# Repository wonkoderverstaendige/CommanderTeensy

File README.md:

# CommanderTeensy
Experimental setup monitor and controller
```
$ cd web
$ python ../commander_teensy/receiver.py
```
Runs webserver on localhost:8000

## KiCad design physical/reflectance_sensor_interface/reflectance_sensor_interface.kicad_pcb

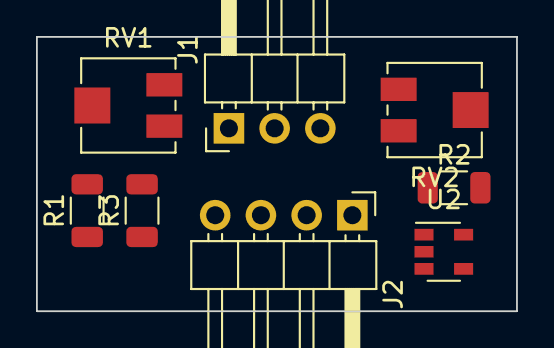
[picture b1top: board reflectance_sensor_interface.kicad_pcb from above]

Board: 2 copper layers, 26.7 x 15.2 mm, 8 parts (0 on the bottom side), 8 nets, no tracks yet.

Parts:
J1: Conn_01x03_Male; PinHeader_1x03_P2.54mm_Horizontal
J2: Conn_01x04_Female; PinHeader_1x04_P2.54mm_Horizontal
R1: 47; R_1206_3216Metric
R2, R3: 100; R_1206_3216Metric
RV1: 1k; Potentiometer_Vishay_TS53YJ_Vertical
RV2: 20k; Potentiometer_Vishay_TS53YJ_Vertical
U2: LM321; SOT-23-5

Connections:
+3V3: J1.3, RV1.1, RV2.1, U2.5
Ln: J1.1, J2.2, J2.4, U2.2
Lp: J2.1, R1.2
unnamed: J1.2, R3.1
unnamed: R1.1, RV1.2
unnamed: R2.1, RV2.2
unnamed: R3.2, U2.3, U2.4
Tc: J2.3, R2.2, U2.1

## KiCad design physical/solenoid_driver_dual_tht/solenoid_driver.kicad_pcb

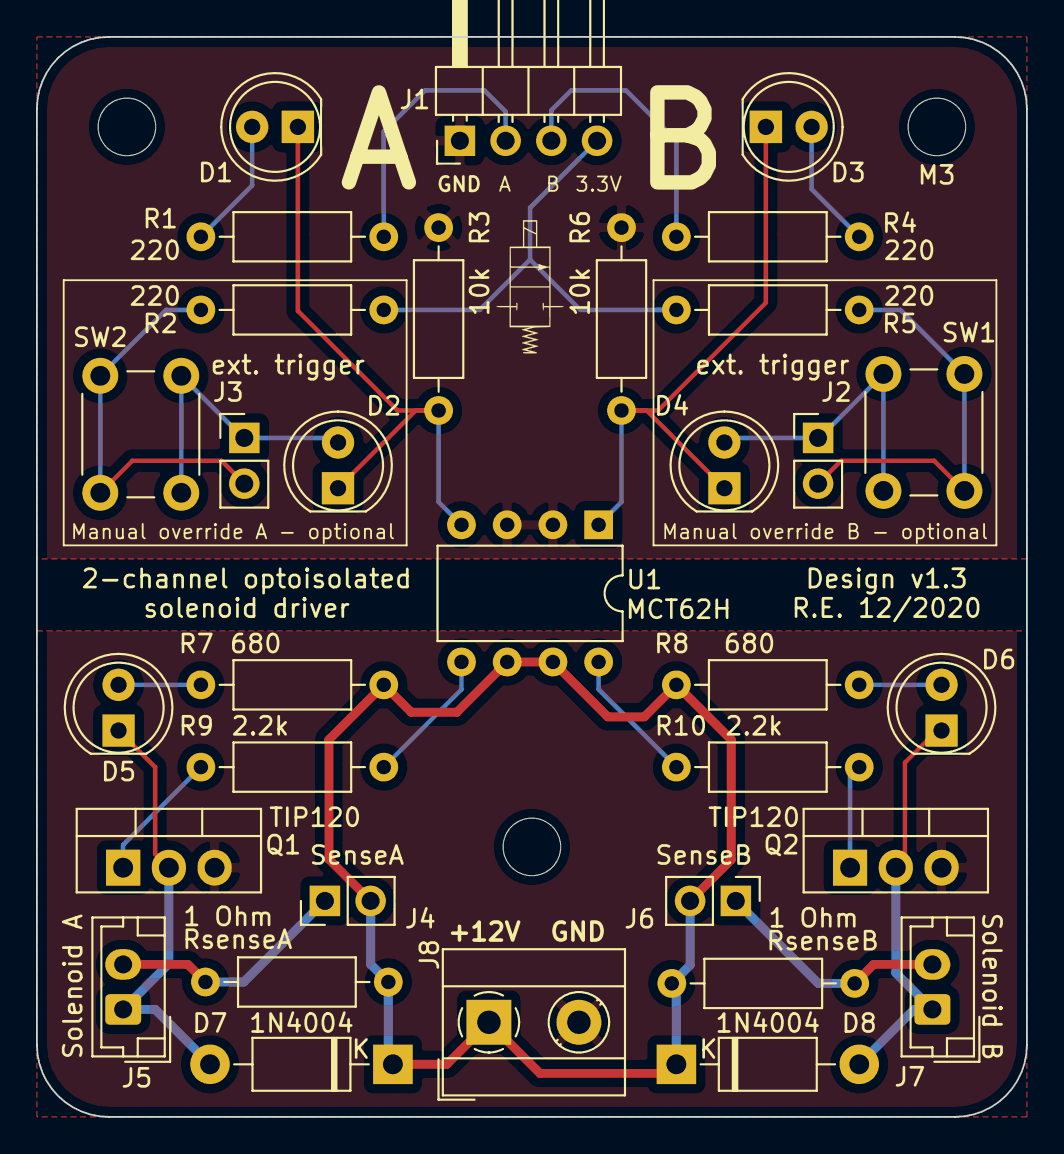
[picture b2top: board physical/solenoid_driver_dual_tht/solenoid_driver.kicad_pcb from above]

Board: 2 copper layers, 55.0 x 60.0 mm, 36 parts (0 on the bottom side), 24 nets.

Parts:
D1, D2, D3, D4, D5, D6: LED; LED_D5.0mm
D7, D8: 1N4004; D_DO-41_SOD81_P10.16mm_Horizontal
J1: Input Header; PinHeader_1x04_P2.54mm_Horizontal
J2: Solenoid B Override; PinHeader_1x02_P2.54mm_Vertical
J3: Solenoid A Override; PinHeader_1x02_P2.54mm_Vertical
J4: SenseA; PinHeader_1x02_P2.54mm_Vertical
J5: Solenoid A; JST_EH_B2B-EH-A_1x02_P2.50mm_Vertical
J6: SenseB; PinHeader_1x02_P2.54mm_Vertical
J7: Solenoid B; JST_EH_B2B-EH-A_1x02_P2.50mm_Vertical
J8: 12V Input; TerminalBlock_MetzConnect_Type055_RT01502HDWU_1x02_P5.00mm_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
M3, M3#2, M3#3: MountingHole_3.2mm_M3
Q1, Q2: TIP120; TO-220-3_Vertical
R1, R2, R4, R5: 220; R_Axial_DIN0207_L6.3mm_D2.5mm_P10.16mm_Horizontal
R3, R6: 10k; R_Axial_DIN0207_L6.3mm_D2.5mm_P10.16mm_Horizontal
R7, R8: 680; R_Axial_DIN0207_L6.3mm_D2.5mm_P10.16mm_Horizontal
R9, R10: 2.2k; R_Axial_DIN0207_L6.3mm_D2.5mm_P10.16mm_Horizontal
RsenseA: 1 Ohm; R_Axial_DIN0207_L6.3mm_D2.5mm_P10.16mm_Horizontal
RsenseB: 1 Ohm; R_Axial_DIN0207_L6.3mm_D2.5mm_P10.16mm_Horizontal
SW1, SW2: SW_Push; SW_PUSH_6mm
U1: MCT62H; DIP-8_W7.62mm

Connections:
3.3V: J1.4, R2.2, R5.2
12V: D7.1, D8.1, J4.2, J6.2, J8.1, R7.2, R8.2, RsenseA.1, RsenseB.1, U1.6, U1.7
GNDPWR: J8.2, Q1.3, Q2.3
InputA: J1.2, R1.2
InputB: J1.3, R4.2
unnamed: D1.1, D2.1, R3.2, U1.4
unnamed: D1.2, R1.1
unnamed: D2.2, J3.1, SW2.2
unnamed: D3.1, D4.1, R6.1, U1.1
unnamed: D3.2, R4.1
unnamed: D4.2, J2.1, SW1.2
unnamed: D5.1, D7.2, J5.1, Q1.2
unnamed: D5.2, R7.1
unnamed: D6.1, D8.2, J7.1, Q2.2
unnamed: D6.2, R8.1
unnamed: J2.2, R5.1, SW1.1
unnamed: J3.2, R2.1, SW2.1
unnamed: J4.1, J5.2, RsenseA.2
unnamed: J6.1, J7.2, RsenseB.2
unnamed: Q1.1, R9.1
unnamed: Q2.1, R10.1
unnamed: R9.2, U1.5
unnamed: R10.2, U1.8
TeensyGND: J1.1, R3.1, R6.2, U1.2, U1.3

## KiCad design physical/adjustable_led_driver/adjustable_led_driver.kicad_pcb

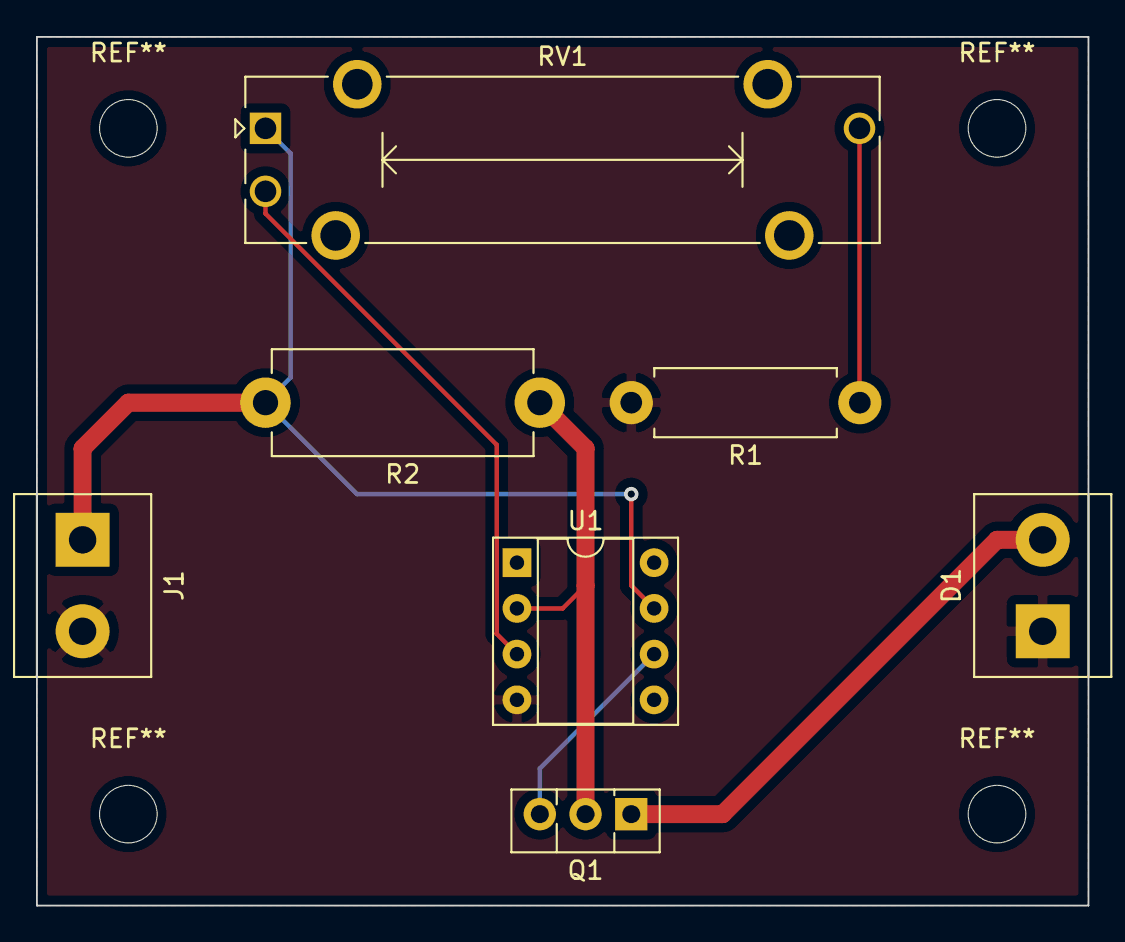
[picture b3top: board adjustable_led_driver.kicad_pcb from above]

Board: 2 copper layers, 58.4 x 48.3 mm, 7 parts (0 on the bottom side), 7 nets.

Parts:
D1: LED; TerminalBlock_bornier-2_P5.08mm
J1: Conn_01x02_Male; TerminalBlock_bornier-2_P5.08mm
Q1: BD140; TO-126-3_Vertical
R1: 1k; R_Axial_DIN0411_L9.9mm_D3.6mm_P12.70mm_Horizontal
R2: 10; R_Axial_DIN0614_L14.3mm_D5.7mm_P15.24mm_Horizontal
RV1: 20k; Potentiometer_Bourns_PTA2043_Single_Slide
U1: LM741; DIP-8_W7.62mm_Socket

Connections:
+5V: J1.1, R2.2, RV1.1, U1.7
GND: D1.1, J1.2, R1.2, U1.4
unnamed: D1.2, Q1.1
unnamed: Q1.2, R2.1, U1.2
unnamed: Q1.3, U1.6
unnamed: R1.1, RV1.3
unnamed: RV1.2, U1.3

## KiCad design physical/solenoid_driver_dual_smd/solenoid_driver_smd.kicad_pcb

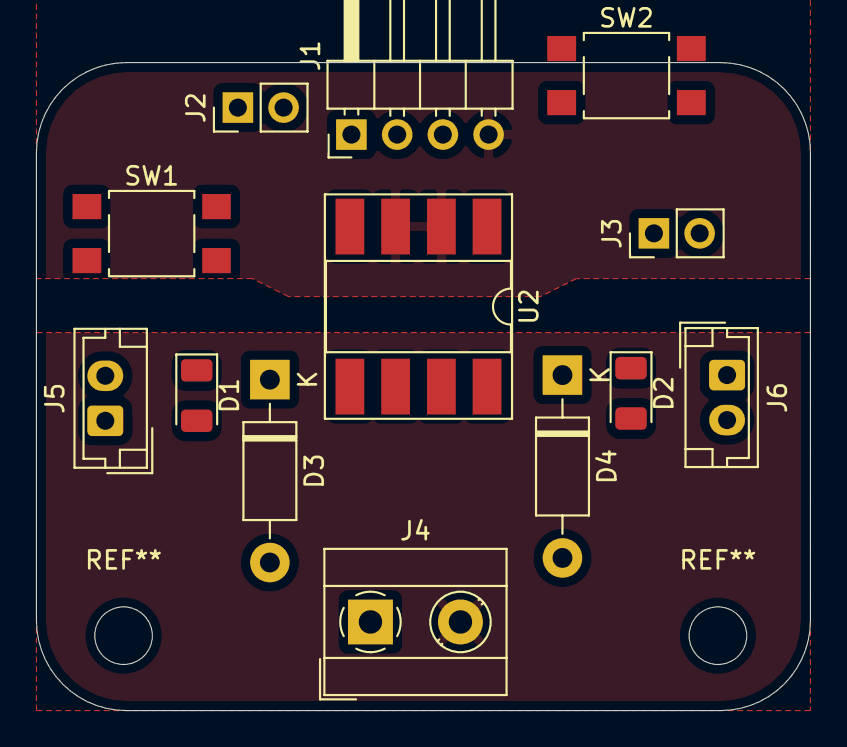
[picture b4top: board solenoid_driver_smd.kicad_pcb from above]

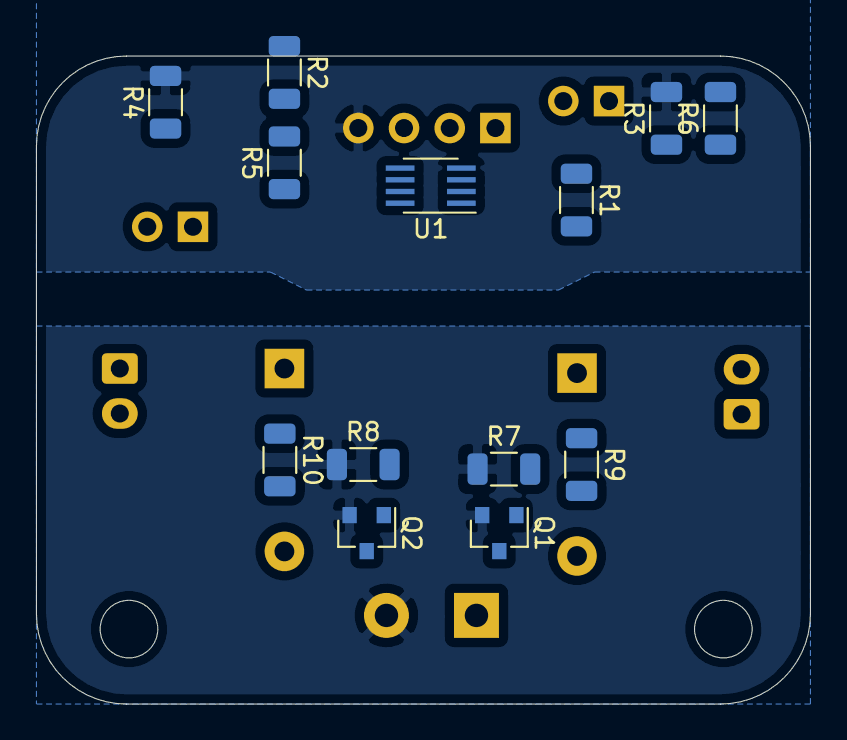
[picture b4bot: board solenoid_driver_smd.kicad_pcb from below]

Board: 2 copper layers, 43.0 x 36.0 mm, 26 parts (13 on the bottom side), 20 nets, no tracks yet.

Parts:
D1, D2: LED; LED_1206_3216Metric
D3, D4: 1N4004; D_DO-41_SOD81_P10.16mm_Horizontal
J1: Input Header; PinHeader_1x04_P2.54mm_Horizontal
J2: ext_trig_A; PinHeader_1x02_P2.54mm_Vertical
J3: ext_trig_B; PinHeader_1x02_P2.54mm_Vertical
J4: PWR12V; TerminalBlock_MetzConnect_Type055_RT01502HDWU_1x02_P5.00mm_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
J5: SolenoidA; JST_EH_B2B-EH-A_1x02_P2.50mm_Vertical
J6: SolenoidB; JST_EH_B2B-EH-A_1x02_P2.50mm_Vertical
Q1, Q2: 2N7002K; SOT-23
R1, R2: 1k; R_1206_3216Metric
R3, R4, R7, R8: 10k; R_1206_3216Metric
R5, R6: 220; R_1206_3216Metric
R9, R10: 680; R_1206_3216Metric
SW1: man_trig_A; SW_SPST_TL3305A
SW2: man_trig_B; SW_SPST_TL3305A
U1: 74LVC2G32; SSOP-8_2.95x2.8mm_P0.65mm
U2: MCT62H; DIP-8_W8.89mm_SMDSocket_LongPads

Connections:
3.3V: J1.1, R1.2, R2.2, U1.8
12V: D3.1, D4.1, J4.1, J5.2, J6.2, R9.1, R10.1, U2.6, U2.7
GNDPWR: J4.2, Q1.2, Q2.2, R7.1, R8.1
InputA: J1.2, U1.1
InputB: J1.3, U1.5
unnamed: D1.1, D3.2, J5.1, Q1.3
unnamed: D1.2, R9.2
unnamed: D2.1, D4.2, J6.1, Q2.3
unnamed: D2.2, R10.2
unnamed: J2.1, R3.1, SW1.2, U1.2
unnamed: J2.2, R1.1, SW1.1
unnamed: J3.1, R4.1, SW2.2, U1.6
unnamed: J3.2, R2.1, SW2.1
unnamed: Q1.1, R7.2, U2.8
unnamed: Q2.1, R8.2, U2.5
unnamed: R5.1, U2.1
unnamed: R5.2, U1.7
unnamed: R6.1, U2.4
unnamed: R6.2, U1.3
TeensyGND: J1.4, R3.2, R4.2, U1.4, U2.2, U2.3

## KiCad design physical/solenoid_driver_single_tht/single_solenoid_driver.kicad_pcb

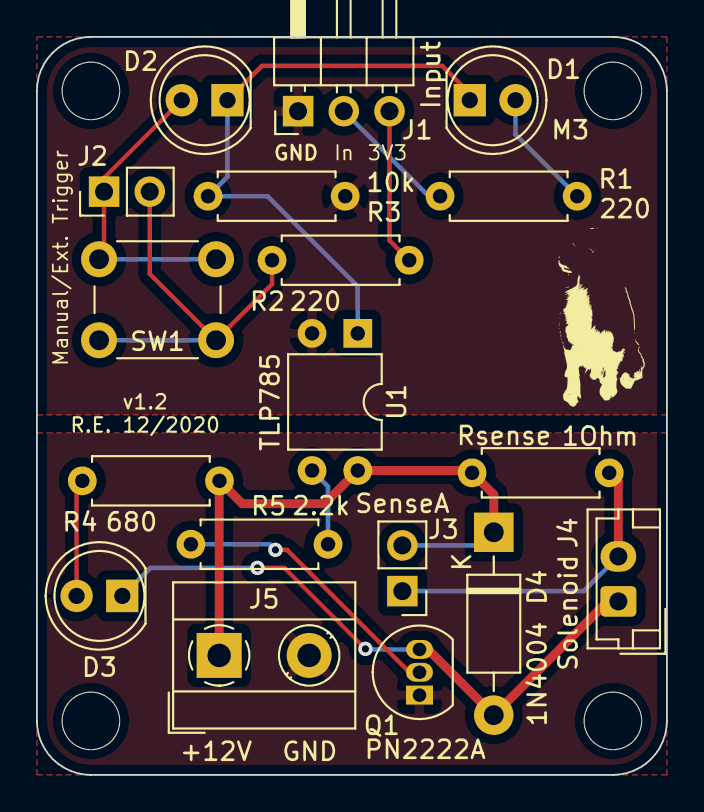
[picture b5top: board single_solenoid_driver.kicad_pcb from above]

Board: 2 copper layers, 35.0 x 41.0 mm, 22 parts (0 on the bottom side), 14 nets.

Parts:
D1, D2, D3: LED; LED_D5.0mm
D4: 1N4004; D_DO-41_SOD81_P10.16mm_Horizontal
J1: Input; PinHeader_1x03_P2.54mm_Horizontal
J2: Manual/External Trigger; PinHeader_1x02_P2.54mm_Vertical
J3: SenseA; PinHeader_1x02_P2.54mm_Vertical
J4: Solenoid; JST_EH_B2B-EH-A_1x02_P2.50mm_Vertical
J5: 12V Input; TerminalBlock_MetzConnect_Type055_RT01502HDWU_1x02_P5.00mm_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
M3, M3#2, M3#3, M3#4: MountingHole_3.2mm_M3
Q1: PN2222A; TO-92_Inline
R1, R2: 220; R_Axial_DIN0207_L6.3mm_D2.5mm_P7.62mm_Horizontal
R3: 10k; R_Axial_DIN0207_L6.3mm_D2.5mm_P7.62mm_Horizontal
R4: 680; R_Axial_DIN0207_L6.3mm_D2.5mm_P7.62mm_Horizontal
R5: 2.2k; R_Axial_DIN0207_L6.3mm_D2.5mm_P7.62mm_Horizontal
Rsense: 1Ohm; R_Axial_DIN0207_L6.3mm_D2.5mm_P7.62mm_Horizontal
SW1: SW_Push; SW_PUSH_6mm
U1: TLP785; DIP-4_W7.62mm

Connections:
3.3V: J1.3, R2.2
12V: D4.1, J3.2, J5.1, R4.2, Rsense.1, U1.4
GNDPWR: J5.2, Q1.1
InputA: J1.2, R1.2
unnamed: D1.1, D2.1, R3.2, U1.1
unnamed: D1.2, R1.1
unnamed: D2.2, J2.1, SW1.2
unnamed: D3.1, D4.2, J4.1, Q1.3
unnamed: D3.2, R4.1
unnamed: J2.2, R2.1, SW1.1
unnamed: J3.1, J4.2, Rsense.2
unnamed: Q1.2, R5.1
unnamed: R5.2, U1.3
TeensyGND: J1.1, R3.1, U1.2

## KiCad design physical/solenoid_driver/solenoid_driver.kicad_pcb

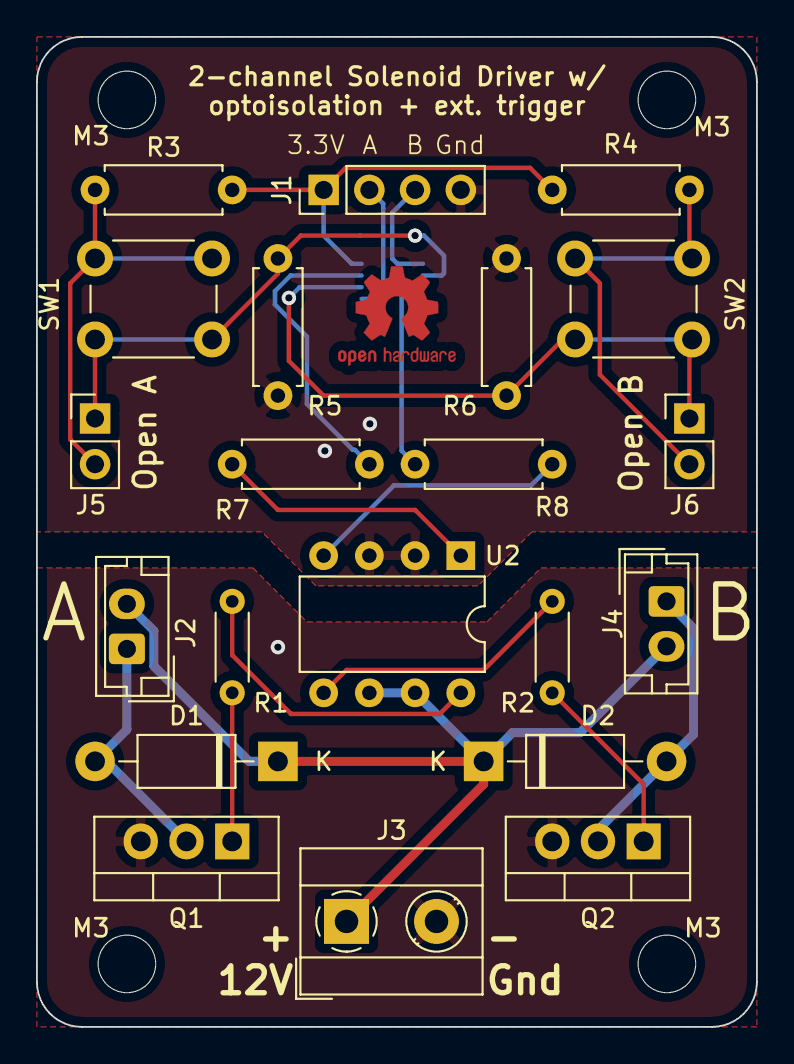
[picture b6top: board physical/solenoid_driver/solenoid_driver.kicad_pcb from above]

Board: 2 copper layers, 40.0 x 55.0 mm, 26 parts (1 on the bottom side), 20 nets.

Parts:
D1, D2: 1N4004; D_DO-41_SOD81_P10.16mm_Horizontal
J1: Input Header; PinHeader_1x04_P2.54mm_Vertical
J2: Solenoid A; JST_EH_B2B-EH-A_1x02_P2.50mm_Vertical
J3: 12V Input; TerminalBlock_MetzConnect_Type055_RT01502HDWU_1x02_P5.00mm_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
J4: Solenoid B; JST_EH_B2B-EH-A_1x02_P2.50mm_Vertical
J5: Solenoid A Override; PinHeader_1x02_P2.54mm_Vertical
J6: Solenoid B Override; PinHeader_1x02_P2.54mm_Vertical
M3, M3#2, M3#3, M3#4: MountingHole_3.2mm_M3
Q1, Q2: TIP120; TO-220-3_Vertical
R1, R2: 2.2k; R_Axial_DIN0204_L3.6mm_D1.6mm_P5.08mm_Horizontal
R3, R4: 1k; R_Axial_DIN0207_L6.3mm_D2.5mm_P7.62mm_Horizontal
R5, R6: 10k; R_Axial_DIN0207_L6.3mm_D2.5mm_P7.62mm_Horizontal
R7, R8: 220; R_Axial_DIN0207_L6.3mm_D2.5mm_P7.62mm_Horizontal
SW1, SW2: SW_Push; SW_PUSH_6mm
U1: 74LVC2G32; SSOP-8_2.95x2.8mm_P0.65mm
U2: ILD74; DIP-8_W7.62mm

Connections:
3.3V: J1.1, R3.2, R4.2, U1.8
12V: D1.1, D2.1, J2.2, J3.1, J4.2, U2.6, U2.7
GNDPWR: J3.2, Q1.3, Q2.3
InputA: J1.3, U1.1
InputB: J1.2, U1.5
unnamed: D1.2, J2.1, Q1.2
unnamed: D2.2, J4.1, Q2.2
unnamed: J5.1, R5.2, SW1.2, U1.2
unnamed: J5.2, R3.1, SW1.1
unnamed: J6.1, R6.2, SW2.2, U1.6
unnamed: J6.2, R4.1, SW2.1
unnamed: Q1.1, R1.1
unnamed: Q2.1, R2.1
unnamed: R1.2, U2.8
unnamed: R2.2, U2.5
unnamed: R7.1, U2.1
unnamed: R7.2, U1.7
unnamed: R8.1, U2.4
unnamed: R8.2, U1.3
TeensyGND: J1.4, R5.1, R6.1, U1.4, U2.2, U2.3

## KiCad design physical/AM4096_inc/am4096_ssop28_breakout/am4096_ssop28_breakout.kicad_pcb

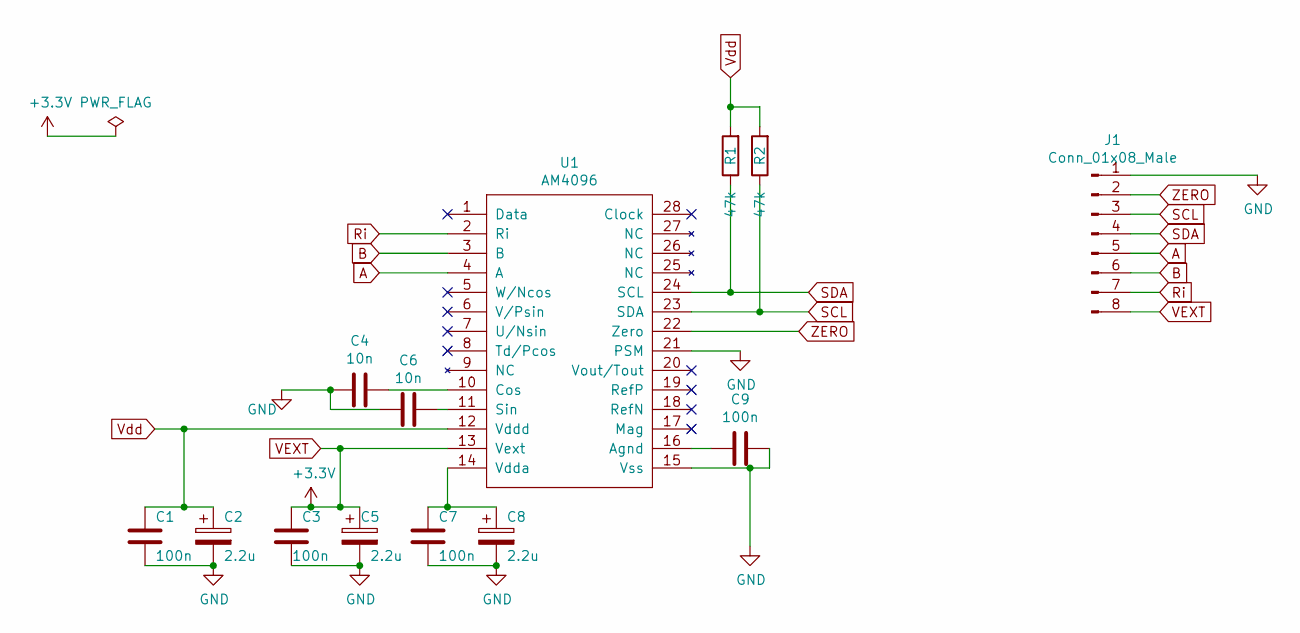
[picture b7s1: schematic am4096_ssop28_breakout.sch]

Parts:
C1, C3, C7: 100n; CP_EIA-3216-18_Kemet-A
C2, C5, C8: 2.2u; CP_EIA-3216-18_Kemet-A
C4, C6: 10n; C_1206_3216Metric
C9: 100n; C_1206_3216Metric
J1: Conn_01x08_Male; Socket_Strip_Straight_1x08_Pitch2.54mm
R1, R2: 47k; R_1206_3216Metric
U1: AM4096; SSOP-28_5.3x10.2mm_P0.65mm

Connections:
A: J1.5, U1.4 (A)
B: J1.6, U1.3 (B)
GND: C1.2, C2.2, C3.2, C4.2, C5.2, C6.2, C7.2, C8.2, C9.1, J1.1, U1.15 (Vss), U1.21 (PSM)
unnamed: C4.1, U1.10 (Cos)
unnamed: C6.1, U1.11 (Sin)
unnamed: C7.1, C8.1, U1.14 (Vdda)
unnamed: C9.2, U1.16 (Agnd)
Ri: J1.7, U1.2 (Ri)
SCL: J1.3, R2.1, U1.23 (SDA)
SDA: J1.4, R1.1, U1.24 (SCL)
VEXT: C3.1, C5.1, J1.8, U1.13 (Vext)
Vdd: C1.1, C2.1, R1.2, R2.2, U1.12 (Vddd)
ZERO: J1.2, U1.22 (Zero)

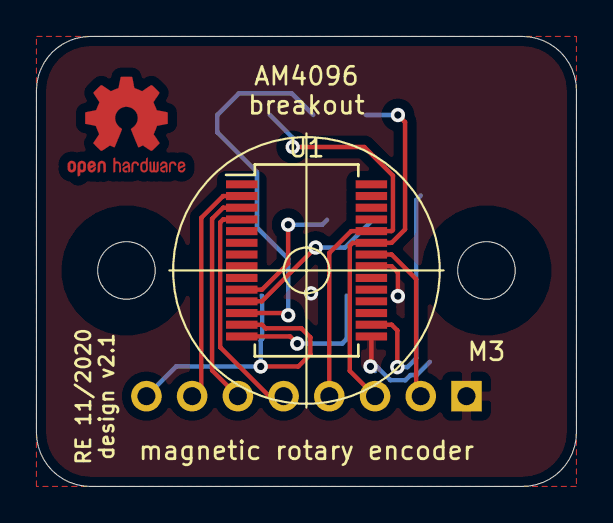
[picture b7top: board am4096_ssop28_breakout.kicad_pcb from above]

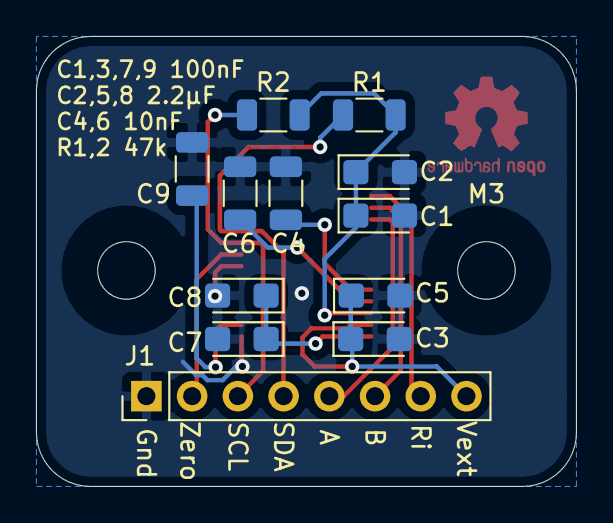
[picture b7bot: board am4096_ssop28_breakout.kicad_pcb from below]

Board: 2 copper layers, 30.0 x 25.0 mm, 15 parts (12 on the bottom side), 13 nets.

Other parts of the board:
M3, M3#2: MountingHole_3.2mm_M3

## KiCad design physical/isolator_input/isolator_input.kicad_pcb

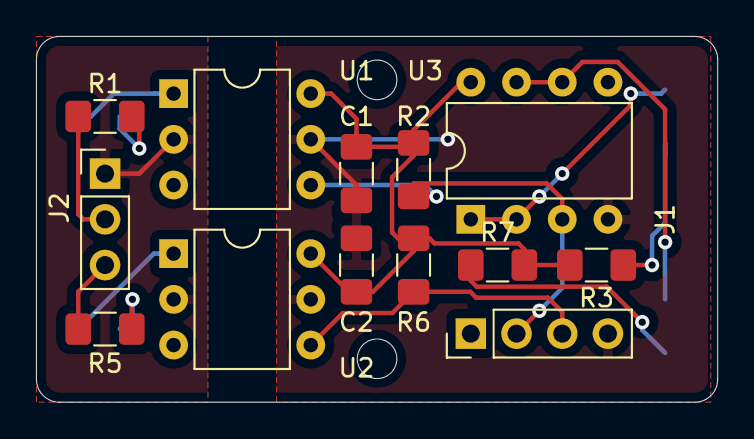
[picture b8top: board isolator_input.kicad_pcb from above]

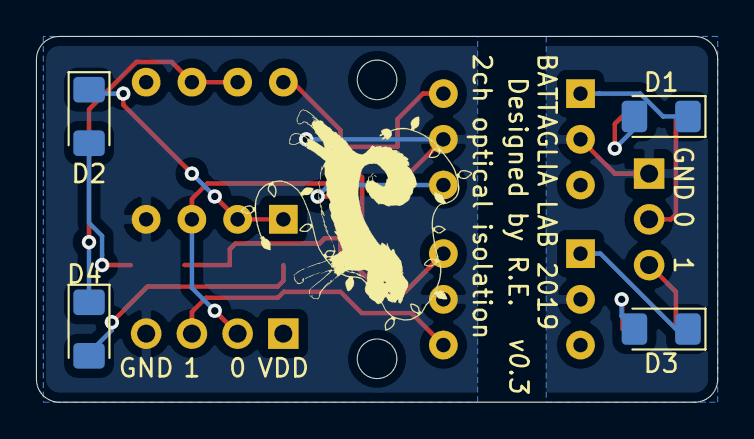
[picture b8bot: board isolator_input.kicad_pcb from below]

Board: 2 copper layers, 37.8 x 20.3 mm, 17 parts (4 on the bottom side), 15 nets.

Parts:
C1, C2: 0.1u; C_1206_3216Metric_Pad1.42x1.75mm_HandSolder
D1, D2, D3, D4: LED; LED_1206_3216Metric_Pad1.42x1.75mm_HandSolder
J1: Conn_01x04_Male; PinHeader_1x04_P2.54mm_Vertical
J2: Conn_01x03_Male; PinHeader_1x03_P2.54mm_Vertical
R1, R3, R5, R7: 330; R_1206_3216Metric_Pad1.42x1.75mm_HandSolder
R2, R6: 4.7k; R_1206_3216Metric_Pad1.42x1.75mm_HandSolder
U1, U2: H11L1; DIP-6_W7.62mm
U3: MCP6002-xSN; DIP-8_W7.62mm

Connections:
GND: J2.1, U1.2, U2.2
GNDA: C1.2, C2.2, J1.4, U1.5, U2.5, U3.4
In01: J2.2, R1.1
In02: J2.3, R5.1
unnamed: D1.1, U1.1
unnamed: D1.2, R1.2
unnamed: D2.1, U3.1, U3.2
unnamed: D2.2, R3.1
unnamed: D3.1, U2.1
unnamed: D3.2, R5.2
unnamed: D4.1, U3.6, U3.7
unnamed: D4.2, R7.1
Out01: J1.2, R2.1, U1.4, U3.3
Out02: J1.3, R6.1, U2.4, U3.5
VDD: C1.1, C2.1, R2.2, R3.2, R6.2, R7.2, U1.6, U2.6, U3.8

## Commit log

2019-10-27 Initial commit of trimmed code
2019-10-27 Add .gitignore
2019-10-27 Add Jetbrains template to .gitignore
2019-10-27 setup.py skeleton
2019-10-27 include python websocket_server module in codebase
2019-10-27 Restructuring...
2019-10-27 Rename favicon.png to favicon.ico to avoid 404
2019-10-27 websocket_server log faulty header GET
2019-10-27 Variable/state chart with dummy values
2019-10-27 Tune state variable visualisation
2019-10-27 Bump state variable field width to 32bit
2019-10-27 LF line termination for base64 encoded packets in log file
2019-10-27 Messing with rainbows and skittles.
2019-10-27 More placeholder variables
2019-11-04 Crudely work around callback buildup during tab blur/inactivity
2019-11-19 M: Unit rename
2019-11-19 Add encoder to teensy
2019-11-27 Initial design of optical isolation board
2019-12-06 opto-isolator board op-amp indicator
2019-12-06 reverse polarity LED indicator
2020-11-04 Housekeeping
2020-11-04 Port selection CLI parameter and file name fix
2020-11-04 Triple serial output from Teensy
2020-11-04 Initial Unity serial port controller
2020-11-04 Rebuilt Unity serial interface for speed and reliability
2020-11-09 Reduce interrupt call size and increase encoder reliability
2020-11-09 Working CRC and added visual feedback
2020-11-09 Remove unused external serial initialization
2020-11-24 Todo updates
2020-11-24 keen and nnm logo images
2020-11-24 Add AM4096 breakout board design
2020-11-26 .gitignore kicad files
2020-11-26 .gitignore kicad bak files
2020-11-26 initial led driver kicad project
2020-11-28 Solenoid driver PCB design
2020-11-28 CRC fault count
2020-12-03 .gitignore kicad autosave files
2020-12-03 solenoid driver board in THT
2020-12-10 Physical: LED driver
2020-12-10 Physical: Solenoid driver boards
2020-12-11 Web backend + curses interface rewrite
2020-12-17 Python streamer log file formatting
2020-12-17 Flush input buffer on serial connection
    Input buffer contains old data not overwritten on buffer overrun.
2021-02-08 Dual THT solenoid PCB updates
2021-05-22 LED driver PCB revision
2021-05-22 solenoid driver PCB revision
2021-05-22 M: Formatting
2021-06-24 Upload pyglet game
2021-07-03 update game & receiver
2021-07-04 Update game & receiver to work again
    Game is working, but we still implement the receiver object in the game class.
2021-07-08 Update websocket usage
2021-07-08 Websocket update
2021-07-08 add comment
2021-07-09 implement sound
2021-07-09 Testing with Zeromq
2021-07-10 Tidying up visualisation.js
2021-07-10 Allow access to web interface from non-localhost sources
2021-07-10 Kick out unused smoothie.js library
2021-07-10 Add handshake assertion to websocket library
2021-07-10 Pull updates from master into Curses Interface
2021-07-10 Add accessible version constant
2021-07-10 Carry over Gerardo's pygame demo
2021-07-10 Send packet data via ZMQ sockets to game
2021-07-10 Remove unused file
2021-07-10 Add commandpacket
2021-07-11 Update game
2021-07-11 Fix packet/s calculation
2021-07-14 Upstream update
2021-07-14 Update imports
2021-07-14 unpack_command_packet
2021-07-15 Upload habituation
2021-07-15 Add random interval
2021-07-16 Loop/gather indication pulses
2021-07-16 Insert instPIN_PULSE
2021-07-16 Remove debug lines
2021-07-16 Reflectance sensor breakout prototype
2021-07-16 Use proper screen width/height and larger block
2021-07-16 Initial refactor upstream communication
2021-07-16 Upload pulse
2021-07-16 Update pinpulse
2021-07-16 Update pinpulse to work again
2021-07-16 correction of game
2021-07-16 Problems with solenoid cmd
2021-07-16 PulsePin
    add setUpTogglePins and getTooglepinById
2021-07-16 websocket server external access. Again.
2021-07-16 Better WS access fix.
2021-07-17 First working version of webgl plotting solution
2021-07-18 Webgl plotting
2021-07-18 pinpulse correction
    added time in future as to not pulse the whole time.
2021-07-18 Condensing init function
2021-07-18 Update nextChangeTime to 0
2021-07-18 Refactoring packaging and instruction handling
2021-07-18 Add missing files...
2021-07-18 Reset game cue movement
2021-07-19 Remove curses dependency on linux
2021-07-19 Skeleton of experiment modules
2021-07-20 Habituation experiment module
2021-07-20 Tem. fix overflow on pulse pins
2021-07-21 current_millis instead of micros
2021-07-21 Desperate measures for pin pulse issues
2021-07-21 Fix logging issues on python<3.9
2021-07-21 Work with elapsedMicros
    Use elapsedMicros and handle rollover
2021-07-22 add habituation day 2
2021-07-22 Add pause function
2021-07-22 Fix habituation day 2
2021-07-22 Add control_screen and fix habituation day 2
2021-07-23 Add wegbl-plot as submodule
2021-07-23 Crude reduced drawing interval to lighten CPU/GPU load for webinterface
2021-07-23 Increase emission frequency SerialDummy
2021-07-23 M: cleanup
2021-07-23 Add Training.py
2021-07-23 remove comments
2021-07-23 use Translationfactor
2021-07-23 rem translation factor
2021-07-24 Quieten debug messages
2021-07-25 Remove unused prototypes
2021-07-25 Restructuring experiments code
2021-07-25 notebook for log reading documentation
2021-07-26 M: cleanup for micros reintroduction
2021-07-28 Camera sync strobing with counter, immediate count
2021-07-28 Better sound/cue presentation on fail and success
2021-07-28 Success ration log message
2021-07-29 Frame interval for camera strobe to prevent blink loss to compression
2021-07-29 Add view of game to webview
2021-07-30 Beginning state messaging
2021-07-30 Training success cue linger period
2021-07-30 WebGL update for better performance
2021-08-06 Make cursesUI optional
2021-08-06 Add binary log file and dummy flags
2021-08-06 Fix HTTP server complaining on quick relaunch
2021-08-06 Reduce websocket server log spam
2021-08-07 Improve reliability and immediacy of toggle buttons in web interface
2021-08-07 Fix wrong order of digital channels in web interface
2021-08-07 Remove legacy web interface files
2021-08-07 Buttons for low/high/toggle digital out interactions in web interface
2021-08-07 Fix decoded message logging using wrong callback
2021-08-08 Multi-part instruction payloads for command packets
2021-08-08 Cue position and visibility as state variables
2021-08-08 Camera and Game canvas objects
2021-08-08 Fix calculation game representation coordinates
2021-08-08 More fixeing calculation game representation coordinates
2021-08-08 Something always slips through...
2021-08-09 Add video to interface
2021-08-09 Upload cam streaming
2021-08-09 MJPEG streamer and h264 recorder
2021-08-09 Version bump to 0.4.1
2021-08-09 Fix hostname not defined for camera stream
2021-08-09 Camera tweaks vol. 1
2021-08-09 Camera tweaks vol. 2
2021-08-09 Camera tweaks vol. 3
2021-08-09 Fix low res video recording
2021-08-09 Log experiment data to file
2021-08-09 Additional command line options for camera operation
2021-08-09 Send trial status as state variable
2021-08-09 Fix aspect ratio of webstream image
2021-08-09 Fix sensor mode paramater
2021-08-09 Make space for actual state variables
2021-08-10 Dependency update
2021-08-10 Lick detection prototype from log
2021-08-10 Fix camera button issues
2021-08-10 Add camera command line entry point
2021-08-10 Prototype sound process
2021-08-10 M: web interface chores
2021-08-10 First attempt at sound fixes
2021-08-10 Second attempt at sound fixes
2021-08-10 Third attempt at sound fixes
2021-08-10 Sound broken...
2021-08-10 Sounddevice issues with multiprocessing
2021-08-10 Attempt to increase nice of sound process
2021-08-10 Giving up on sound fix
2021-08-11 Maybe fix http server scoping issue
2021-08-11 Maybe now fix http server scoping issue
2021-08-12 Javascript import to esm.js
2021-08-16 Fix logging and add screen resolution argument
2021-08-16 Smoother keyboard input when moving cursor
2021-08-18 Update web interface
2021-08-18 De-biasing of trial side for repeat trials
2021-08-18 Ramping for sound onset and offset
2021-08-18 Teensy side reset instruction
2021-08-18 add sound pyglet
2021-08-18 Lower volume and decrease wheel sensitivity
2021-08-18 Send reset packet on start
2021-08-19 Web interface
2021-08-19 Match file naming of camera to rest of log files
2021-08-19 Fix custom resolution breaking raspberry display
2021-08-19 Disable keyboard input, which breaks on the pi
2021-08-19 Remove unused game canvas prototype
2021-08-19 Fix video stream aspect ratio not maintained
2021-08-19 web interface tweaks
2021-08-19 More web interface tweaks
2021-08-20 Fix debiasing direction
2021-08-21 Really fix debiasing
2021-09-10 b64+cobs log to bin conversion tool
2021-09-10 Crude Matlab conversion call and memmap plotting
